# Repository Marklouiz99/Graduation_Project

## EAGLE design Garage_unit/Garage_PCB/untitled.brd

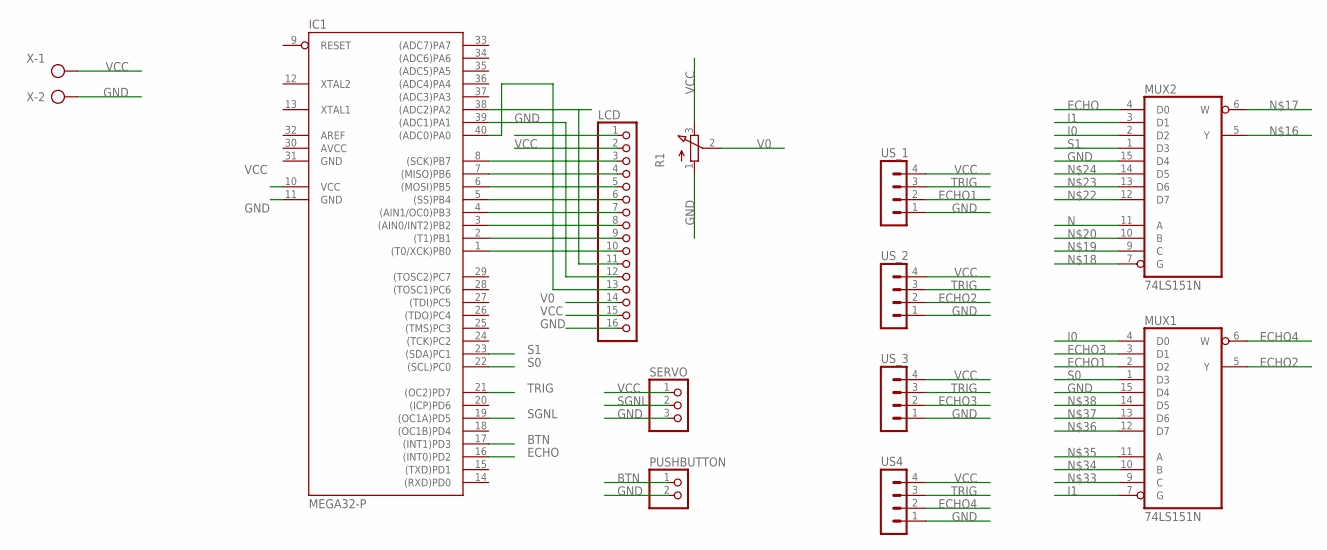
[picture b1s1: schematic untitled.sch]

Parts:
IC1: MEGA32-P; DIL40
LCD: PINHD-1X16; 1X16
MUX1, MUX2: 74LS151N; DIL16
PUSHBUTTON: PINHD-1X2; 1X02
R1: 3RP/1610N
SERVO: PINHD-1X3; 1X03
US4: MA04-1
US_1, US_2, US_3: MA04-1
X: AK300/2

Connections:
AVCC: IC1.30 (AVCC)
BTN: IC1.17 ((INT1)PD3), PUSHBUTTON.1
ECHO: IC1.16 ((INT0)PD2), MUX2.4 (D0)
ECHO1: MUX1.2 (D2), US_1.2
ECHO2: MUX1.5 (Y), US_2.2
ECHO3: MUX1.3 (D1), US_3.2
ECHO4: MUX1.6 (W), US4.2
GND: IC1.11 (GND), IC1.31 (GND), LCD.1, LCD.16, MUX1.8 (GND), MUX1.15 (D4), MUX2.8 (GND), MUX2.15 (D4), PUSHBUTTON.2, R1.1 (A), SERVO.3, US4.1, US_1.1, US_2.1, US_3.1, X.2
I0: MUX1.4 (D0), MUX2.2 (D2)
I1: MUX1.7 (G), MUX2.3 (D1)
N: MUX2.11 (A)
unnamed: IC1.38 ((ADC2)PA2), LCD.11
unnamed: IC1.39 ((ADC1)PA1), LCD.12
unnamed: IC1.8 ((SCK)PB7), LCD.3
unnamed: IC1.7 ((MISO)PB6), LCD.4
unnamed: IC1.6 ((MOSI)PB5), LCD.5
unnamed: IC1.5 ((SS)PB4), LCD.6
unnamed: IC1.4 ((AIN1/OC0)PB3), LCD.7
unnamed: IC1.3 ((AIN0/INT2)PB2), LCD.8
unnamed: IC1.2 ((T1)PB1), LCD.9
unnamed: IC1.1 ((T0/XCK)PB0), LCD.10
unnamed: IC1.40 ((ADC0)PA0), LCD.13
S0: IC1.22 ((SCL)PC0), MUX1.1 (D3)
S1: IC1.23 ((SDA)PC1), MUX2.1 (D3)
SGNL: IC1.19 ((OC1A)PD5), SERVO.2
TRIG: IC1.21 ((OC2)PD7), US4.3, US_1.3, US_2.3, US_3.3
V0: LCD.14, R1.2 (S)
VCC: IC1.10 (VCC), LCD.2, LCD.15, MUX1.16 (VCC), MUX2.16 (VCC), R1.3 (E), SERVO.1, US4.4, US_1.4, US_2.4, US_3.4, X.1

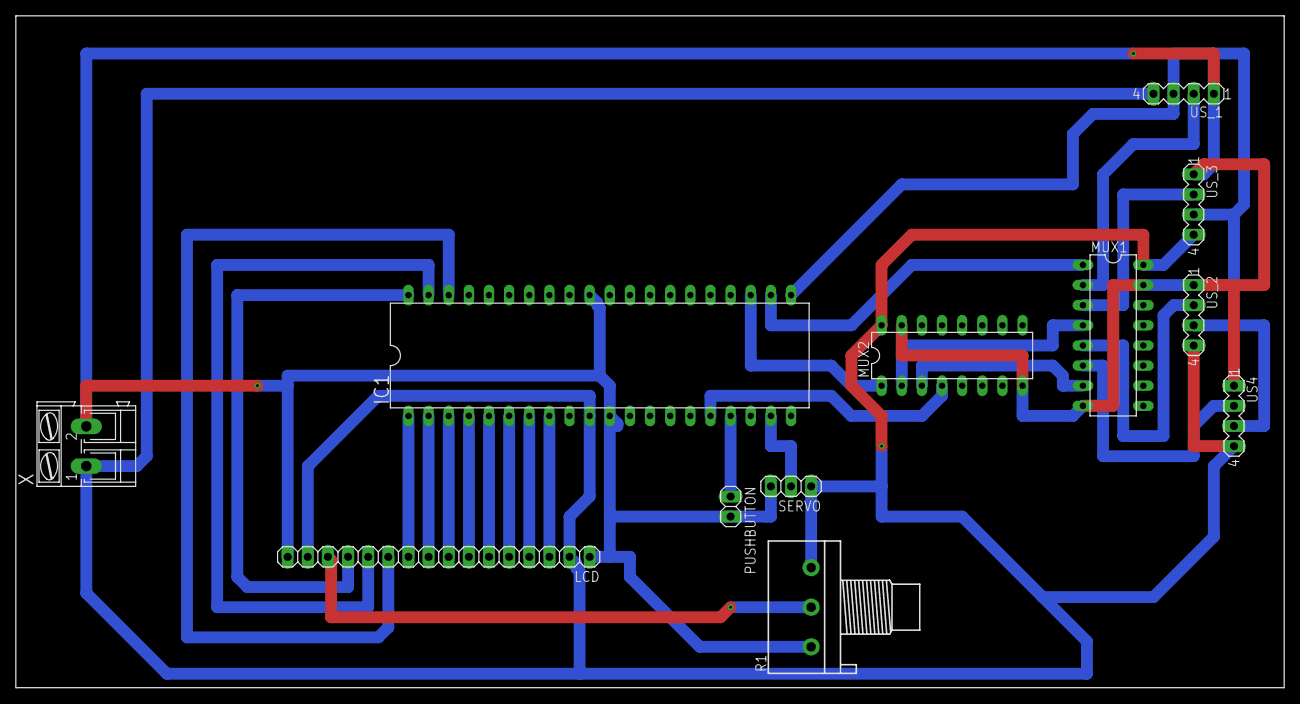
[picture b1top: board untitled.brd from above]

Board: 2 copper layers, 160.0 x 84.8 mm, 12 parts (0 on the bottom side), 26 nets.
